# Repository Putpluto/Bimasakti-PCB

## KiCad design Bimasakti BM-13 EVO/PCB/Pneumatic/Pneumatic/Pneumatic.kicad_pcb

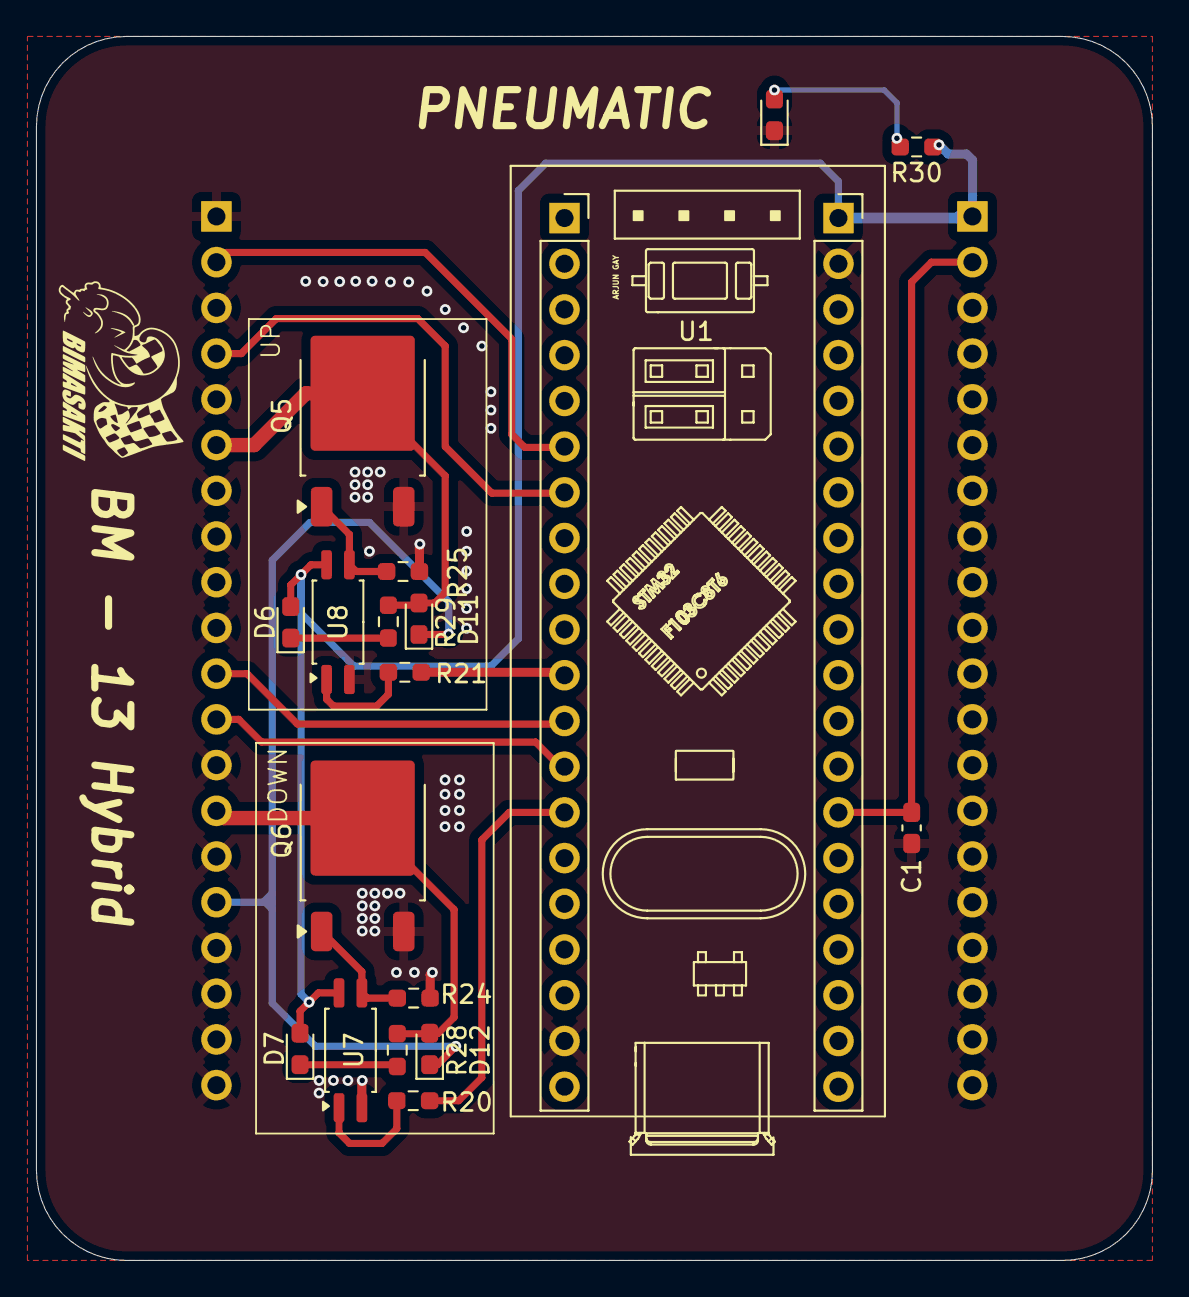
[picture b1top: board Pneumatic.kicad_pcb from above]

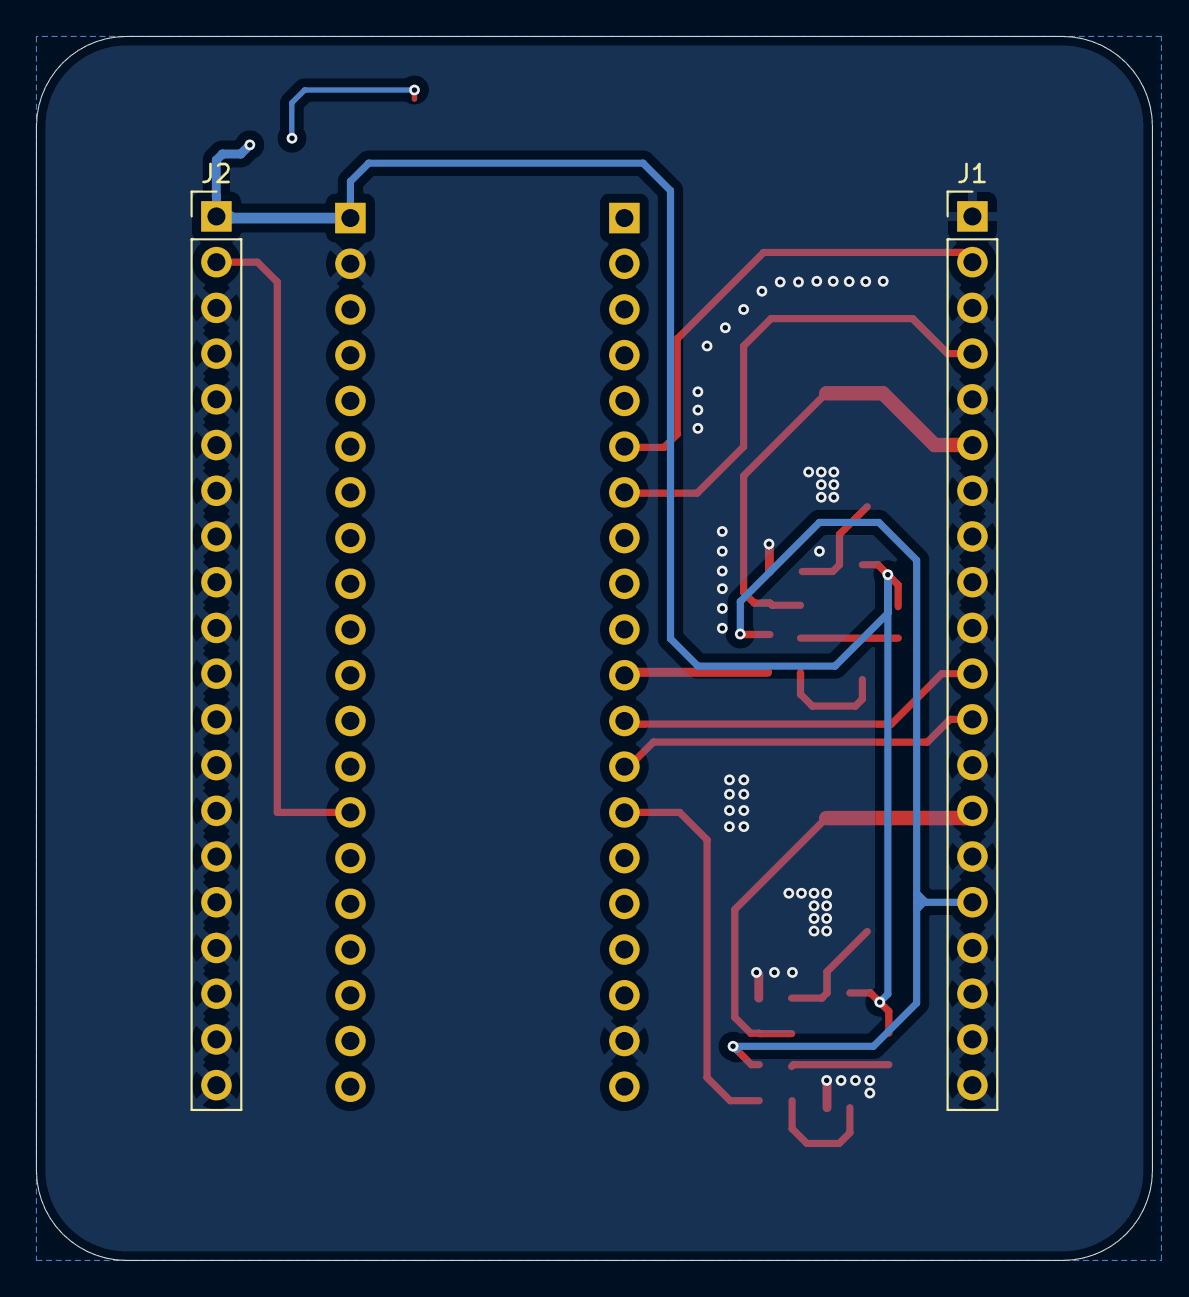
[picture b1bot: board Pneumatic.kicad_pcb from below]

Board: 2 copper layers, 62.0 x 68.0 mm, 20 parts (2 on the bottom side), 19 nets.

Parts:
C1: 0.1uF; C_0603_1608Metric_Pad1.08x0.95mm_HandSolder
D6, D7, D8: LED; LED_0603_1608Metric_Pad1.05x0.95mm_HandSolder
D11, D12: D; D_0603_1608Metric_Pad1.05x0.95mm_HandSolder
J1, J2: Conn_01x20_Pin; PinHeader_1x20_P2.54mm_Vertical
Q5, Q6: DMTH6004SK3; TO-252-2
R20, R21: 330; R_0603_1608Metric_Pad0.98x0.95mm_HandSolder
R24, R25: 10K; R_0603_1608Metric_Pad0.98x0.95mm_HandSolder
R28, R29, R30: 1K; R_0603_1608Metric_Pad0.98x0.95mm_HandSolder
U1: Blackpill PLT
U7, U8: TCMT1103; SOP-4_4.4x2.6mm_P1.27mm

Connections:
+5V: D6.2 (A), D7.2 (A), J2.1, R30.1, U1.1 (5V), U7.4, U8.4
+12V: D11.1 (K), D12.1 (K), J1.16
/DOWNSHIFT: R20.1, U1.18 (PB6)
/Down: J1.12, U1.17 (PB5)
/Pneumatic_DOWN: D12.2 (A), J1.14, Q6.2 (D), R28.2
/Pneumatic_UP: D11.2 (A), J1.6, Q5.2 (D), R29.2
/RX: J1.4, U1.11 (PA10)
/TX: J1.2, U1.10 (PA9)
/UP: J1.11, U1.16 (PB4)
/UPSHIFT: R21.1, U1.15 (PB3)
GND: C1.1, D8.1 (K), J1.1, J1.3, J1.5, J1.7, J1.8, J1.9, J1.10, J1.13, J1.15, J1.17, J1.18, J1.19, J1.20, J2.3, J2.4, J2.5, J2.6, J2.7, J2.8, J2.9, J2.10, J2.11, J2.12, J2.13, J2.14, J2.15, J2.16, J2.17, J2.18, J2.19, J2.20, Q5.3 (S), Q6.3 (S), R24.1, R25.1, U1.39 (GND), U1.40 (GND), U7.2, U8.2
GPOS: C1.2, J2.2, U1.32 (PA1)
unnamed: D6.1 (K), R29.1
unnamed: D7.1 (K), R28.1
unnamed: D8.2 (A), R30.2
unnamed: Q5.1 (G), R25.2, U8.3
unnamed: Q6.1 (G), R24.2, U7.3
unnamed: R20.2, U7.1
unnamed: R21.2, U8.1

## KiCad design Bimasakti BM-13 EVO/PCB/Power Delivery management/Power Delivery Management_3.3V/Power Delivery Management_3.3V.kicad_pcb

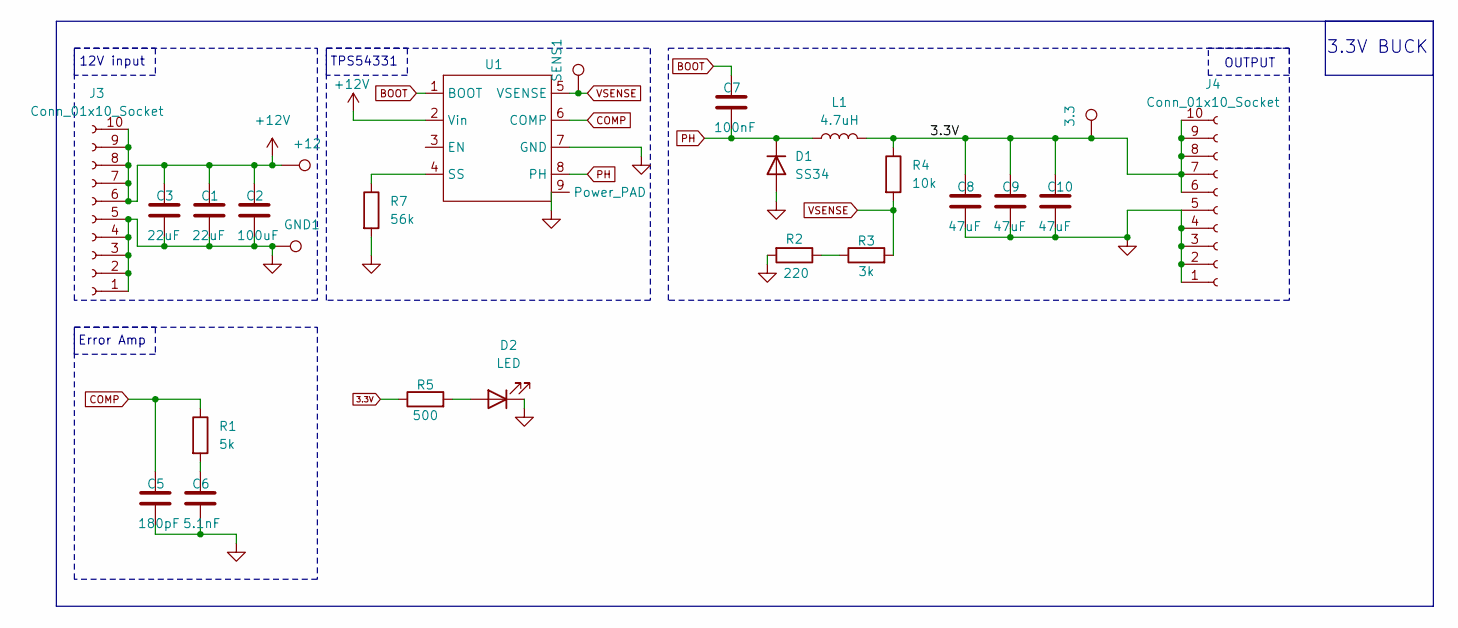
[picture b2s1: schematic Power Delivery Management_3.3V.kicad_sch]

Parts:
3.3: TestPoint; TestPoint_Bridge_Pitch2.0mm_Drill0.7mm
+12: TestPoint; TestPoint_Bridge_Pitch2.0mm_Drill0.7mm
C1, C3: 22uF; C_1210_3225Metric
C2: 100uF; C_1210_3225Metric
C5: 180pF; C_0603_1608Metric
C6: 5.1nF; C_0603_1608Metric
C7: 100nF; C_0603_1608Metric
C8, C9, C10: 47uF; C_0603_1608Metric
D1: SS34; D_SMA
D2: LED; LED_0603_1608Metric_Pad1.05x0.95mm_HandSolder
GND1: TestPoint; TestPoint_Bridge_Pitch2.0mm_Drill0.7mm
J3, J4: Conn_01x10_Socket; PinHeader_1x10_P2.54mm_Vertical
L1: 4.7uH; L_Changjiang_FNR5020S
R1: 5k; R_0603_1608Metric
R2: 220; R_0603_1608Metric
R3: 3k; R_0603_1608Metric
R4: 10k; R_0603_1608Metric
R5: 500; R_0603_1608Metric
R7: 56k; R_0603_1608Metric
SENS1: TestPoint; TestPoint_Bridge_Pitch2.0mm_Drill0.7mm
U1: TI_SO-PowerPAD-8

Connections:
3.3V: 3.3.1, C8.1, C9.1, C10.1, J4.6, J4.7, J4.8, J4.9, J4.10, L1.2, R4.1, R5.1
+12V: +12.1, C1.1, C2.1, C3.1, J3.6, J3.7, J3.8, J3.9, J3.10, U1.2 (Vin)
BOOT: C7.1, U1.1 (BOOT)
COMP: C5.1, R1.1, U1.6 (COMP)
GND: C1.2, C2.2, C3.2, C5.2, C6.2, C8.2, C9.2, C10.2, D1.2 (A), D2.1 (K), GND1.1, J3.1, J3.2, J3.3, J3.4, J3.5, J4.1, J4.2, J4.3, J4.4, J4.5, R2.2, R7.2, U1.7 (GND), U1.9 (Power_PAD)
unnamed: C6.1, R1.2
unnamed: D2.2 (A), R5.2
unnamed: R2.1, R3.1
unnamed: R7.1, U1.4 (SS)
PH: C7.2, D1.1 (K), L1.1, U1.8 (PH)
VSENSE: R3.2, R4.2, SENS1.1, U1.5 (VSENSE)

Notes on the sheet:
3.3V BUCK
OUTPUT
Error Amp
TPS54331
12V input

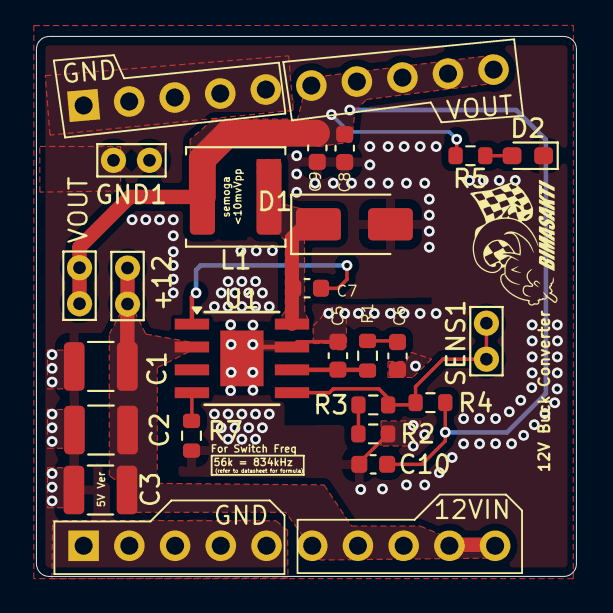
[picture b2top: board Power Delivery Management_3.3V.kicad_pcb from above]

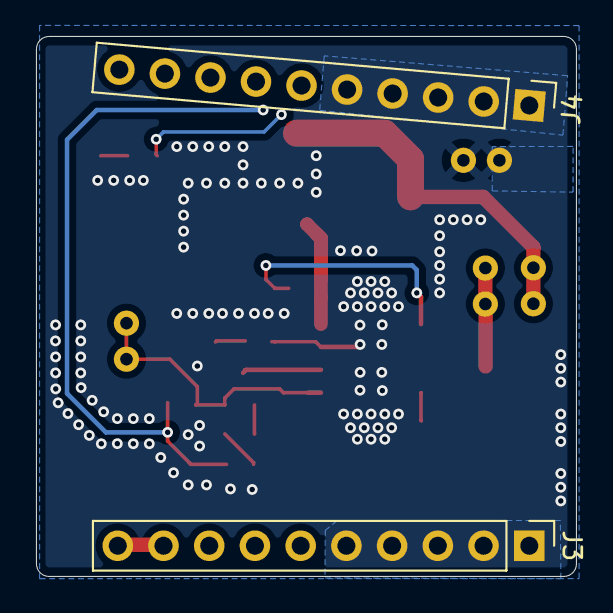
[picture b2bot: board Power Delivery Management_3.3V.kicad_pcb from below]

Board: 4 copper layers, 30.0 x 30.0 mm, 25 parts (2 on the bottom side), 11 nets.

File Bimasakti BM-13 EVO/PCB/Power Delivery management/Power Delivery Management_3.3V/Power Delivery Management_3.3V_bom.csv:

"Reference";"Value";"Footprint";"Datasheet";"Qty";"DNP"
"U1";"~";"Package_SO:TI_SO-PowerPAD-8";"";"1";""
"R7";"56k";"Resistor_SMD:R_0603_1608Metric";"~";"1";""
"R5";"500";"Resistor_SMD:R_0603_1608Metric";"~";"1";""
"R4";"10k";"Resistor_SMD:R_0603_1608Metric";"~";"1";""
"R3";"3k";"Resistor_SMD:R_0603_1608Metric";"~";"1";""
"R2";"220";"Resistor_SMD:R_0603_1608Metric";"~";"1";""
"R1";"5k";"Resistor_SMD:R_0603_1608Metric";"~";"1";""
"L1";"4.7uH";"Inductor_SMD:L_Changjiang_FNR5020S";"~";"1";""
"J3J4";"Conn_01x10_Socket";"Connector_PinHeader_2.54mm:PinHeader_1x10_P2.54mm_Vertical";"~";"2";""
"D2";"LED";"LED_SMD:LED_0603_1608Metric_Pad1.05x0.95mm_HandSolder";"~";"1";""
"D1";"SS34";"Diode_SMD:D_SMA";"~";"1";""
"C8C9C10";"47uF";"Capacitor_SMD:C_0603_1608Metric";"~";"3";""
"C7";"100nF";"Capacitor_SMD:C_0603_1608Metric";"~";"1";""
"C6";"5.1nF";"Capacitor_SMD:C_0603_1608Metric";"~";"1";""
"C5";"180pF";"Capacitor_SMD:C_0603_1608Metric";"~";"1";""
"C2";"100uF";"Capacitor_SMD:C_1210_3225Metric";"~";"1";""
"C1C3";"22uF";"Capacitor_SMD:C_1210_3225Metric";"~";"2";""
"+123.3GND1SENS1";"TestPoint";"TestPoint:TestPoint_Bridge_Pitch2.0mm_Drill0.7mm";"~";"4";""

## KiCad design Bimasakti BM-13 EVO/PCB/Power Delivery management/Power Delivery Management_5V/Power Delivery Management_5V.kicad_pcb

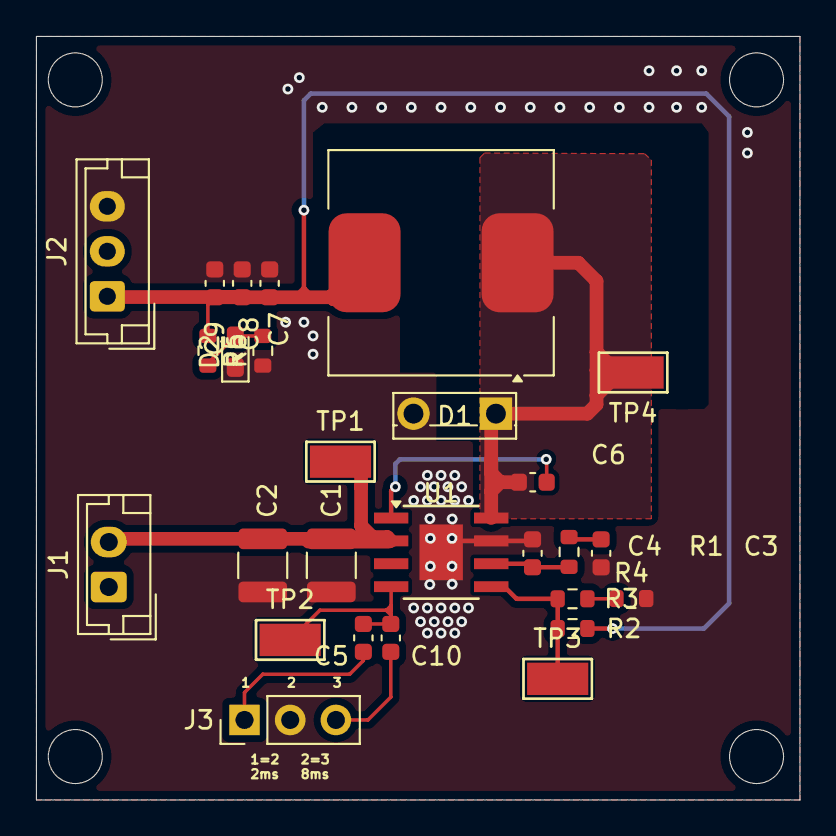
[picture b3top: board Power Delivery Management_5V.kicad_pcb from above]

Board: 4 copper layers, 42.4 x 42.4 mm, 27 parts (0 on the bottom side), 13 nets.

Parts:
C1, C2: 22uF; C_1210_3225Metric
C3: 1nF; C_0603_1608Metric
C4: 10pF; C_0603_1608Metric
C5: 5nF; C_0603_1608Metric
C6: 100nF; C_0603_1608Metric
C7, C8, C9: 47uF; C_0603_1608Metric
C10: 20nF; C_0603_1608Metric
D1: 950mV 10A; TO-251-2_Vertical
D2: LED; LED_0603_1608Metric_Pad1.05x0.95mm_HandSolder
J1: +12V In; JST_EH_B2B-EH-A_1x02_P2.50mm_Vertical
J2: Conn_01x03_Socket; JST_EH_B3B-EH-A_1x03_P2.50mm_Vertical
J3: Slow Start; PinHeader_1x03_P2.54mm_Vertical
L1: 12uH; L_Coilcraft_MSS1278T-XXX
R1: 50k; R_0603_1608Metric
R2: 10k; R_0603_1608Metric
R3, R6: 1.5k; R_0603_1608Metric
R4: 390; R_0603_1608Metric
R5: 1k; R_0603_1608Metric
TP1, TP2, TP3, TP4: TestPoint; TestPoint_Keystone_5015_Micro-Minature
U1: TI_SO-PowerPAD-8

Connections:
+5v: C7.1, C8.1, C9.1, J2.1, L1.2, R2.1, R5.1
+12V: C1.1, C2.1, TP1.1, U1.2 (Vin)
BOOT: C6.1, U1.1 (BOOT)
COMP: C4.1, R1.1, U1.6 (COMP)
GND: C1.2, C2.2, C3.2, C4.2, C7.2, C8.2, C9.2, D1.2 (A), D2.1 (K), J2.3, J3.2, R4.2, R6.1, U1.7 (GND), U1.9 (Power_PAD)
unnamed: C3.1, R1.2
unnamed: D2.2 (A), R5.2, R6.2
unnamed: R3.1, R4.1
unnamed: C5.2, C10.2, TP2.1, U1.4 (SS)
PH: C6.2, D1.1 (K), L1.1, TP4.1, U1.8 (PH)
SS1: C5.1, J3.1
SS2: C10.1, J3.3
VSENSE: R2.2, R3.2, TP3.1, U1.5 (VSENSE)

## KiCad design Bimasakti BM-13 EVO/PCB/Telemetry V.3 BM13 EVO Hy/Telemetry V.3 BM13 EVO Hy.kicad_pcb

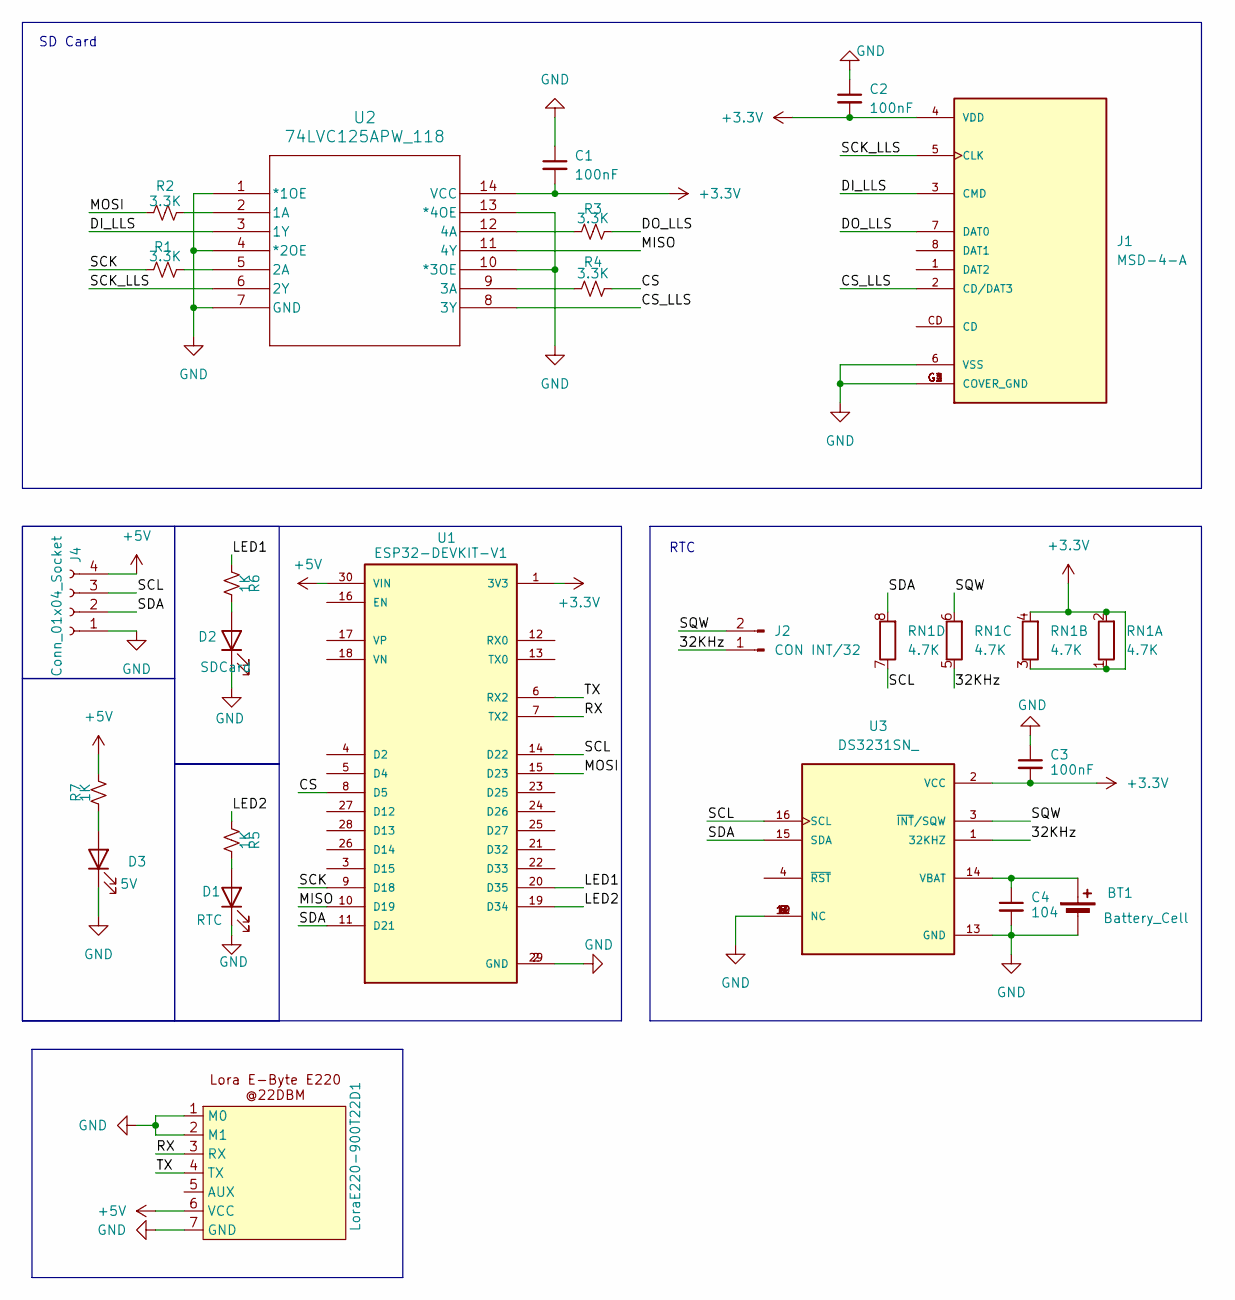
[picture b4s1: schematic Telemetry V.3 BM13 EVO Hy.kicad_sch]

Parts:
BT1: Battery_Cell; BatteryHolder_MYOUNG_BS-07-A1BJ001_CR2032
C1, C2, C3: 100nF; C_0603_1608Metric_Pad1.08x0.95mm_HandSolder
C4: 104; C_0603_1608Metric_Pad1.08x0.95mm_HandSolder
D1: RTC; LED_0603_1608Metric_Pad1.05x0.95mm_HandSolder
D2: SDCard; LED_0603_1608Metric_Pad1.05x0.95mm_HandSolder
D3: 5V; LED_0603_1608Metric_Pad1.05x0.95mm_HandSolder
J1: MSD-4-A; CUI_MSD-4-A; PARTREV 1.0
J2: CON INT/32; PinHeader_1x02_P2.54mm_Vertical
J4: Conn_01x04_Socket; JST_XH_B4B-XH-A_1x04_P2.50mm_Vertical
LoraE220-900T22D1: Lora E220-900T22D
R1, R2, R3, R4: 3.3K; R_0603_1608Metric_Pad0.98x0.95mm_HandSolder
R5, R6, R7: 1K; R_0603_1608Metric_Pad0.98x0.95mm_HandSolder
RN1: 4.7K; R_Array_Convex_4x0603
U1: ESP32-DEVKIT-V1; MODULE_ESP32_DEVKIT_V1; PARTREV N/A
U2: 74LVC125APW_118; TSSOP14_SOT402-1_NEX
U3: DS3231SN_; SOIC127P1032X265-16N; PARTREV 10

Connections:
+3.3V: C1.2, C2.2, C3.2, J1.4 (VDD), RN1.1 (R1.1), RN1.2 (R1.2), RN1.3 (R2.1), RN1.4 (R2.2), U1.1 (3V3), U2.14 (VCC), U3.2 (VCC)
+5V: J4.4, LoraE220-900T22D1.6 (VCC), R7.2, U1.30 (VIN)
/32KHz: J2.1, RN1.5 (R3.1), U3.1 (32KHZ)
/CS: R4.2, U1.8 (D5)
/CS_LLS: J1.2 (CD/DAT3), U2.8 (3Y)
/DI_LLS: J1.3 (CMD), U2.3 (1Y)
/DO_LLS: J1.7 (DAT0), R3.2
/LED1: R6.1, U1.20 (D35)
/LED2: R5.1, U1.19 (D34)
/MISO: U1.10 (D19), U2.11 (4Y)
/MOSI: R2.1, U1.15 (D23)
/RX: LoraE220-900T22D1.3 (RX), U1.7 (TX2)
/SCK: R1.1, U1.9 (D18)
/SCK_LLS: J1.5 (CLK), U2.6 (2Y)
/SCL: J4.3, RN1.7 (R4.1), U1.14 (D22), U3.16 (SCL)
/SDA: J4.2, RN1.8 (R4.2), U1.11 (D21), U3.15 (SDA)
/SQW: J2.2, RN1.6 (R3.2), U3.3 (~INT/SQW)
/TX: LoraE220-900T22D1.4 (TX), U1.6 (RX2)
GND: BT1.2 (-), C1.1, C2.1, C3.1, C4.2, D1.1 (K), D2.1 (K), D3.1 (K), J1.6 (VSS), J1.G1 (COVER_GND), J1.G2 (COVER_GND), J1.G3 (COVER_GND), J1.G4 (COVER_GND), J4.1, LoraE220-900T22D1.1 (M0), LoraE220-900T22D1.2 (M1), LoraE220-900T22D1.7 (GND), U1.2 (GND), U1.29 (GND), U2.1 (*1OE), U2.4 (*2OE), U2.7 (GND), U2.10 (*3OE), U2.13 (*4OE), U3.5 (NC), U3.6 (NC), U3.7 (NC), U3.8 (NC), U3.9 (NC), U3.10 (NC), U3.11 (NC), U3.12 (NC), U3.13 (GND)
unnamed: BT1.1 (+), C4.1, U3.14 (VBAT)
unnamed: D1.2 (A), R5.2
unnamed: D2.2 (A), R6.2
unnamed: D3.2 (A), R7.1
unnamed: R2.2, U2.2 (1A)
unnamed: R1.2, U2.5 (2A)
unnamed: R4.1, U2.9 (3A)
unnamed: R3.1, U2.12 (4A)

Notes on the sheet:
RTC
SD Card

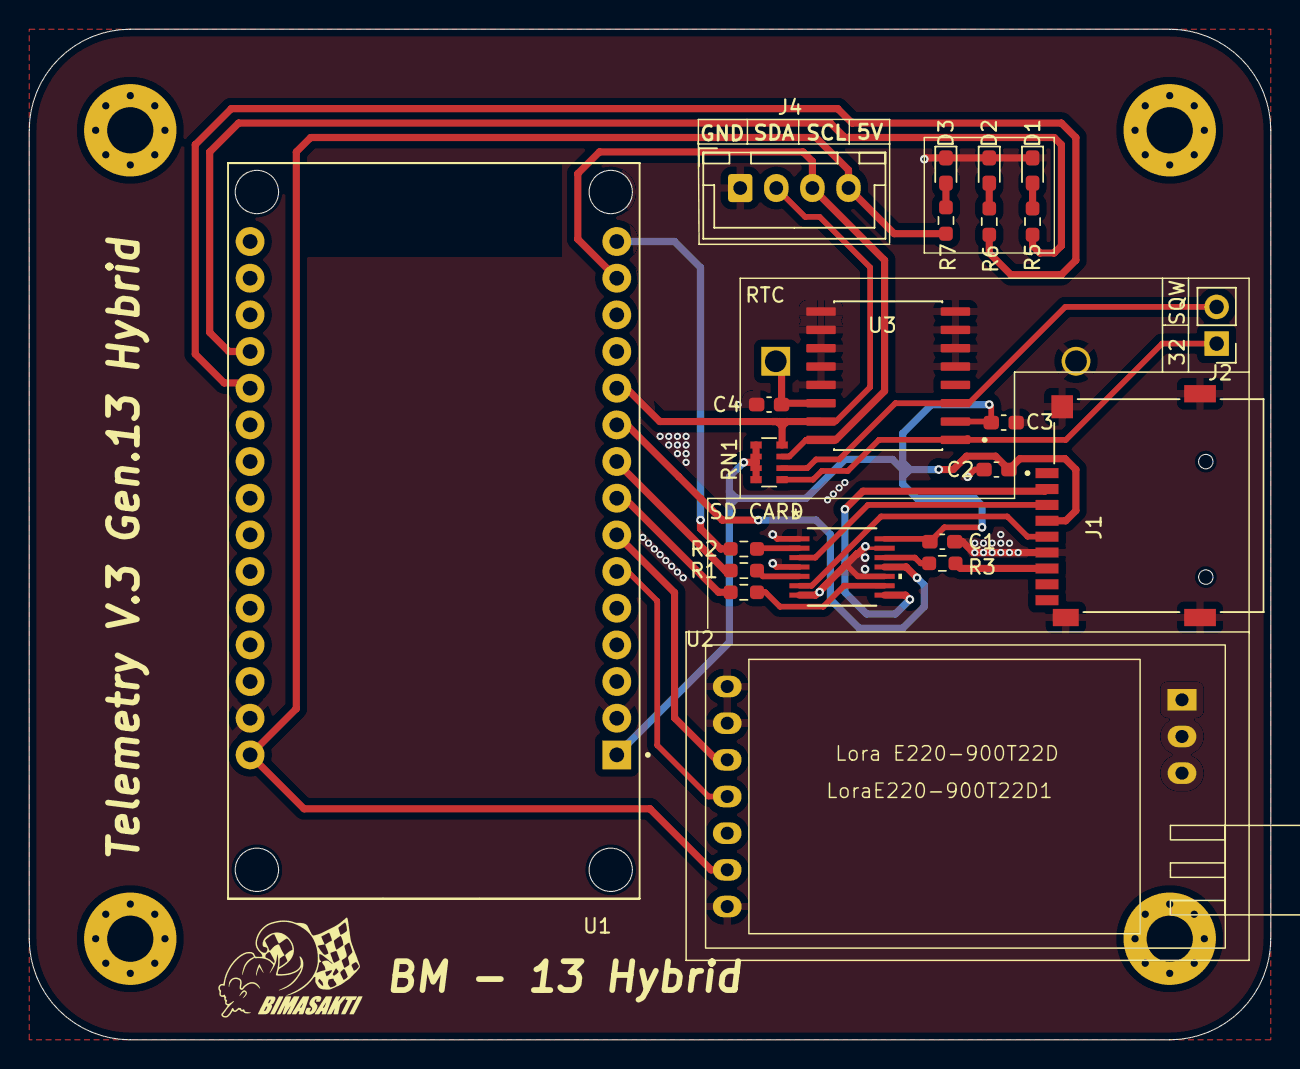
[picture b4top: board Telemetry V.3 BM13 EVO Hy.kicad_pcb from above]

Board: 2 copper layers, 86.0 x 70.0 mm, 23 parts (1 on the bottom side), 27 nets.

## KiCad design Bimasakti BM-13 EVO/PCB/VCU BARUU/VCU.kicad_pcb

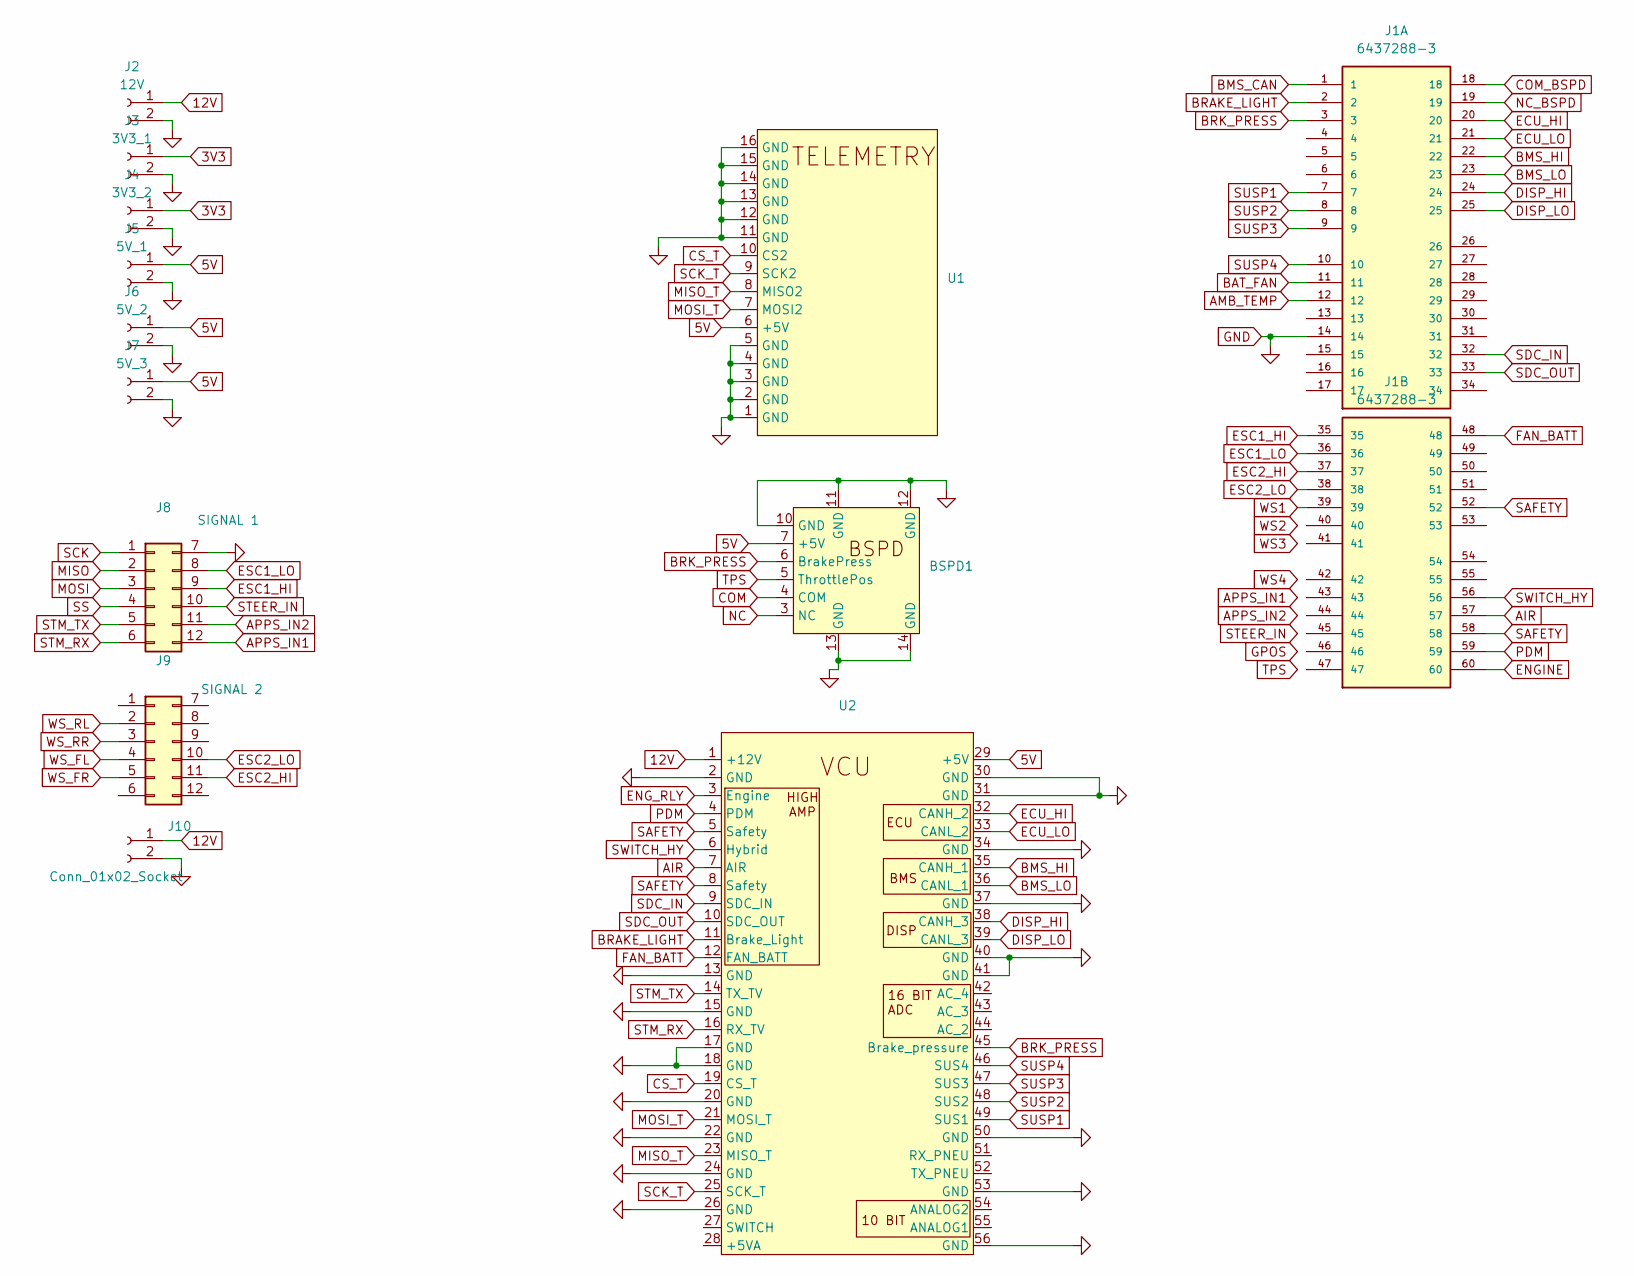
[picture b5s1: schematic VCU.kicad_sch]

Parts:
BSPD1: FootPrintBPSD
J1: 6437288-3; VCU_CONNECTOR_TE_6437288-3; PARTREV A1
J2: 12V; JST_XH_B2B-XH-A_1x02_P2.50mm_Vertical
J3: 3V3_1; JST_XH_B2B-XH-A_1x02_P2.50mm_Vertical
J4: 3V3_2; JST_XH_B2B-XH-A_1x02_P2.50mm_Vertical
J5: 5V_1; JST_XH_B2B-XH-A_1x02_P2.50mm_Vertical
J6: 5V_2; JST_XH_B2B-XH-A_1x02_P2.50mm_Vertical
J7: 5V_3; JST_XH_B2B-XH-A_1x02_P2.50mm_Vertical
J8: SIGNAL 1; Molex_Nano-Fit_105310-xx12_2x06_P2.50mm_Vertical
J9: SIGNAL 2; Molex_Nano-Fit_105310-xx12_2x06_P2.50mm_Vertical
J10: Conn_01x02_Socket; Molex_Nano-Fit_105309-xx02_1x02_P2.50mm_Vertical
U1: 0_FootprintTelemetry
U2: FootprintVCU

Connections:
3V3: J3.1, J4.1
5V: BSPD1.7 (+5V), J5.1, J6.1, J7.1, U1.6 (+5V), U2.29 (+5V)
12V: J2.1, J10.1, U2.1 (+12V)
AIR: J1.57, U2.7 (AIR)
AMB_TEMP: J1.12
APPS_IN1: J8.12
APPS_IN2: J8.11
BAT_FAN: J1.11
BMS_CAN: J1.1
BMS_HI: J1.22, U2.35 (CANH_1)
BMS_LO: J1.23, U2.36 (CANL_1)
BRAKE_LIGHT: J1.2, U2.11 (Brake_Light)
BRK_PRESS: BSPD1.6 (BrakePress), J1.3, U2.45 (Brake_pressure)
COM: BSPD1.4 (COM)
COM_BSPD: J1.18
CS_T: U1.10 (CS2), U2.19 (CS_T)
DISP_HI: J1.24, U2.38 (CANH_3)
DISP_LO: J1.25, U2.39 (CANL_3)
ECU_HI: J1.20, U2.32 (CANH_2)
ECU_LO: J1.21, U2.33 (CANL_2)
ENGINE: J1.60
ENG_RLY: U2.3 (Engine)
ESC1_HI: J1.35, J8.9
ESC1_LO: J1.36, J8.8
ESC2_HI: J1.37, J9.11
ESC2_LO: J1.38, J9.10
FAN_BATT: J1.48, U2.12 (FAN_BATT)
GND: BSPD1.10 (GND), BSPD1.11 (GND), BSPD1.12 (GND), BSPD1.13 (GND), BSPD1.14 (GND), J1.14, J2.2, J3.2, J4.2, J5.2, J6.2, J7.2, J8.7, J10.2, U1.1 (GND), U1.2 (GND), U1.3 (GND), U1.4 (GND), U1.5 (GND), U1.11 (GND), U1.12 (GND), U1.13 (GND), U1.14 (GND), U1.15 (GND), U1.16 (GND), U2.2 (GND), U2.13 (GND), U2.15 (GND), U2.17 (GND), U2.18 (GND), U2.20 (GND), U2.22 (GND), U2.24 (GND), U2.26 (GND), U2.30 (GND), U2.31 (GND), U2.34 (GND), U2.37 (GND), U2.40 (GND), U2.41 (GND), U2.50 (GND), U2.53 (GND), U2.56 (GND)
MISO: J8.2
MISO_T: U1.8 (MISO2), U2.23 (MISO_T)
MOSI: J8.3
MOSI_T: U1.7 (MOSI2), U2.21 (MOSI_T)
NC: BSPD1.3 (NC)
NC_BSPD: J1.19
PDM: J1.59, U2.4 (PDM)
SAFETY: J1.52, J1.58, U2.5 (Safety), U2.8 (Safety)
SCK: J8.1
SCK_T: U1.9 (SCK2), U2.25 (SCK_T)
SDC_IN: J1.32, U2.9 (SDC_IN)
SDC_OUT: J1.33, U2.10 (SDC_OUT)
SS: J8.4
STEER_IN: J8.10
STM_RX: J8.6, U2.16 (RX_TV)
STM_TX: J8.5, U2.14 (TX_TV)
SUSP1: J1.7, U2.49 (SUS1)
SUSP2: J1.8, U2.48 (SUS2)
SUSP3: J1.9, U2.47 (SUS3)
SUSP4: J1.10, U2.46 (SUS4)
SWITCH_HY: J1.56, U2.6 (Hybrid)
TPS: BSPD1.5 (ThrottlePos)
WS1: J1.39
WS_FL: J9.4
WS_FR: J9.5
WS_RL: J9.2
WS_RR: J9.3

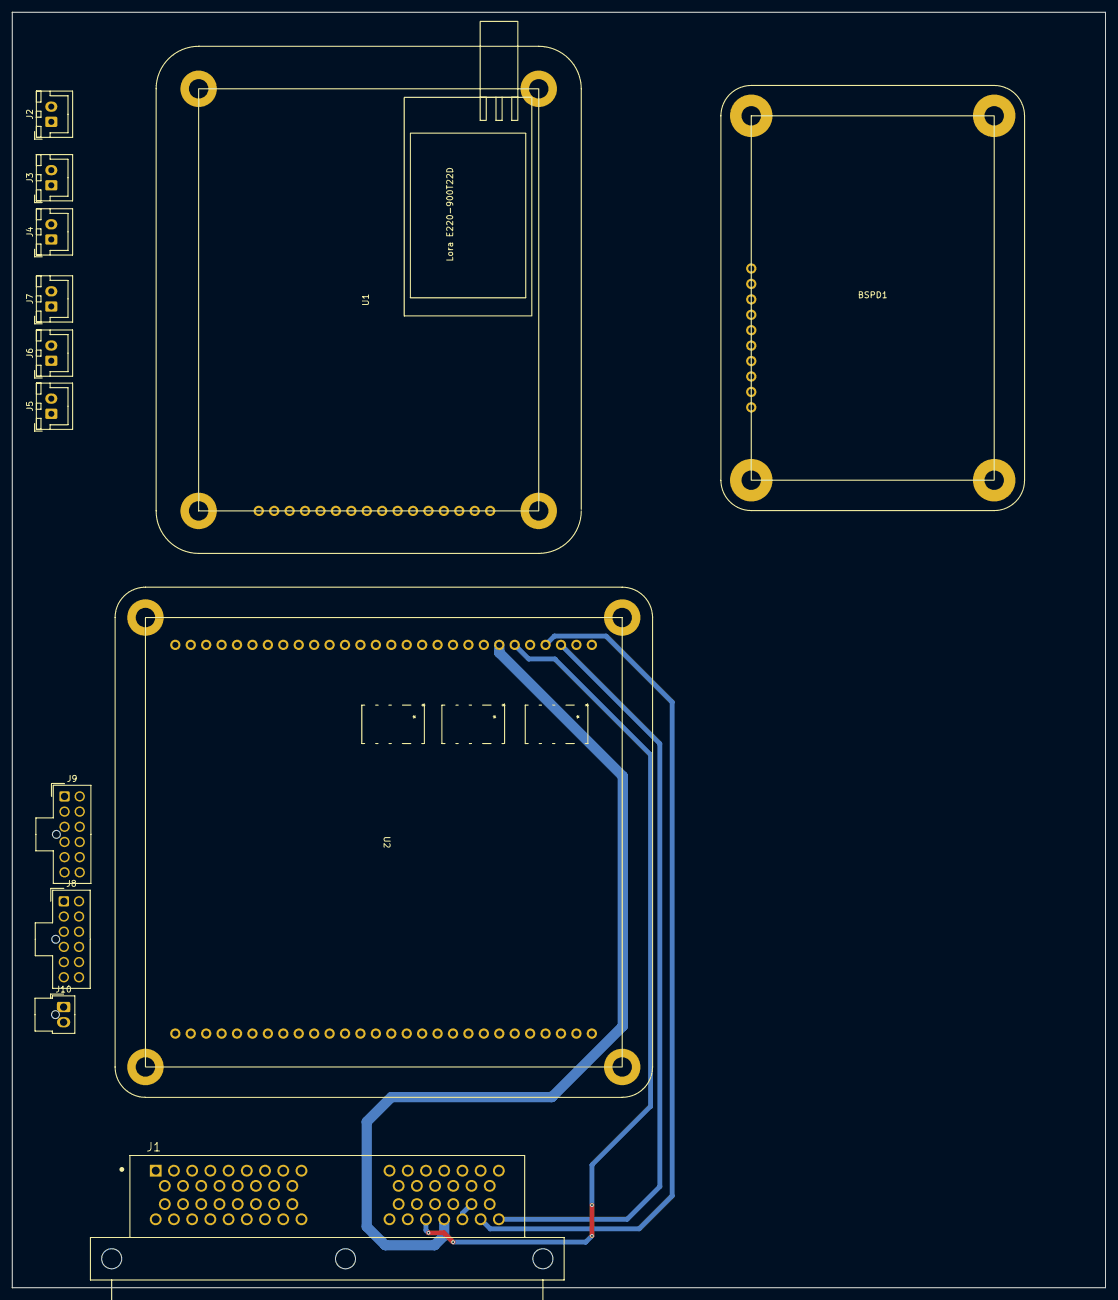
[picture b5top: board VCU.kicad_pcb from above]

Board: 2 copper layers, 180.0 x 210.0 mm, 13 parts (0 on the bottom side), 33 nets.

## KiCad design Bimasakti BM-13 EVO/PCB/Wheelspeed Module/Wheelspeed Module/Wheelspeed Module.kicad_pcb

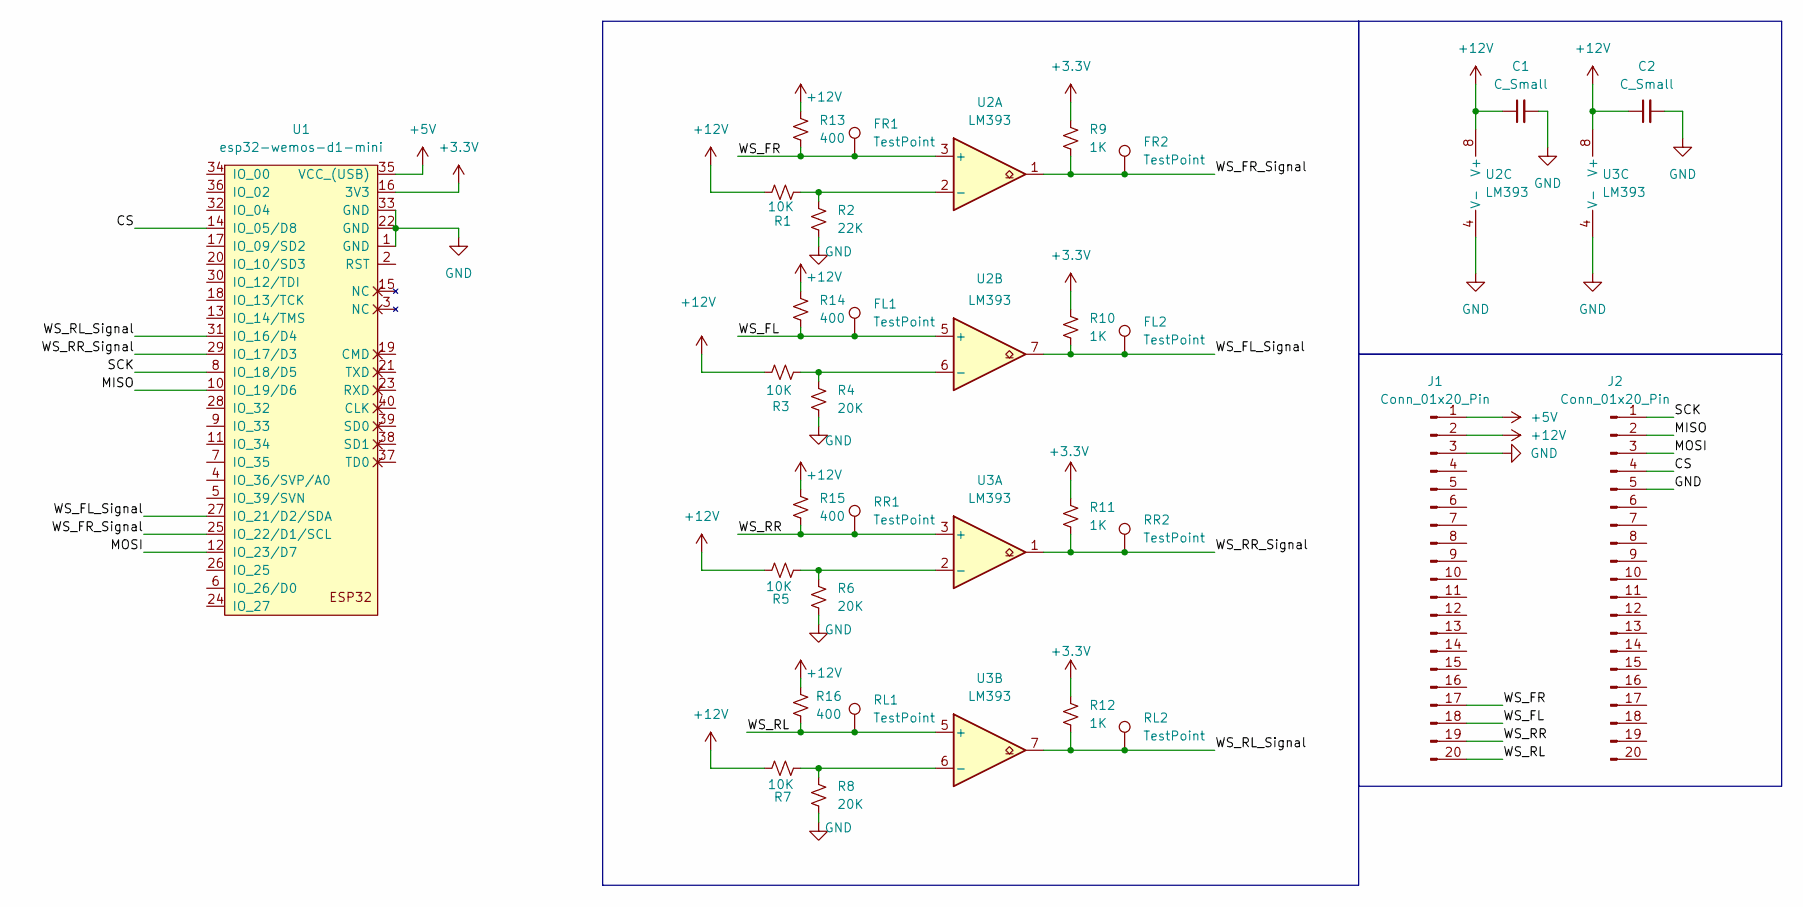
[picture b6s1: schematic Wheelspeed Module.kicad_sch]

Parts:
C1, C2: C_Small; C_0603_1608Metric_Pad1.08x0.95mm_HandSolder
FL1, FL2: TestPoint; TestPoint_Bridge_Pitch2.54mm_Drill0.7mm
FR1, FR2: TestPoint; TestPoint_Bridge_Pitch2.54mm_Drill0.7mm
J1, J2: Conn_01x20_Pin; PinHeader_1x20_P2.54mm_Vertical
R1, R3, R5, R7: 10K; R_0603_1608Metric_Pad0.98x0.95mm_HandSolder
R2: 22K; R_0603_1608Metric_Pad0.98x0.95mm_HandSolder
R4, R6, R8: 20K; R_0603_1608Metric_Pad0.98x0.95mm_HandSolder
R9, R10, R11, R12: 1K; R_0603_1608Metric_Pad0.98x0.95mm_HandSolder
R13, R14, R15, R16: 400; R_0603_1608Metric_Pad0.98x0.95mm_HandSolder
RL1, RL2: TestPoint; TestPoint_Bridge_Pitch2.54mm_Drill0.7mm
RR1, RR2: TestPoint; TestPoint_Bridge_Pitch2.54mm_Drill0.7mm
U1: esp32-wemos-d1-mini
U2, U3: LM393; SO8_STM

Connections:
+3.3V: R9.1, R10.1, R11.1, R12.1, U1.16 (3V3)
+5V: J1.1, U1.35 (VCC_(USB))
+12V: C1.1, C2.1, J1.2, R1.1, R3.1, R5.1, R7.1, R13.1, R14.1, R15.1, R16.1, U2.8 (V+), U3.8 (V+)
/CS: J2.4, U1.14 (IO_05/D8)
/MISO: J2.2, U1.10 (IO_19/D6)
/MOSI: J2.3, U1.12 (IO_23/D7)
/SCK: J2.1, U1.8 (IO_18/D5)
/WS_FL: FL1.1, J1.18, R14.2, U2.5 (+)
/WS_FL_Signal: FL2.1, R10.2, U1.27 (IO_21/D2/SDA), U2.7
/WS_FR: FR1.1, J1.17, R13.2, U2.3 (+)
/WS_FR_Signal: FR2.1, R9.2, U1.25 (IO_22/D1/SCL), U2.1
/WS_RL: J1.20, R16.2, RL1.1, U3.5 (+)
/WS_RL_Signal: R12.2, RL2.1, U1.31 (IO_16/D4), U3.7
/WS_RR: J1.19, R15.2, RR1.1, U3.3 (+)
/WS_RR_Signal: R11.2, RR2.1, U1.29 (IO_17/D3), U3.1
GND: C1.2, C2.2, J1.3, J2.5, R2.2, R4.2, R6.2, R8.2, U1.1 (GND), U1.22 (GND), U1.33 (GND), U2.4 (V-), U3.4 (V-)
unnamed: R1.2, R2.1, U2.2 (-)
unnamed: R3.2, R4.1, U2.6 (-)
unnamed: R5.2, R6.1, U3.2 (-)
unnamed: R7.2, R8.1, U3.6 (-)
